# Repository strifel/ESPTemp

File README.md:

# ESPTemp

A small ambient sensor PCB powered by an ESP32-C3 an BME280 or BME680

## Parts

| **Part** |  **Description** |
| -------- | ---------------- |
| U1       | ESP32-C3-WROOM   |
| U2       | TLV1117-3.3V     |
| U3       | BME280           |
| U4       | BME680           |
| D1       | WS2812B LED      |
| R1,R2    | 5.1k Resistor    |
| R3,R5,R6 | 10k Resistor     |
| R4       | 1k Resistor      |
| C1,C4    | 100 uF Capacitor |
| C2       | 1 uF Capacitor   |
| C4       | 10 uF Capacitor  |
| J1       | USB_C_Receptable |
| J2       | 3-Pin-Connector  |

## Software

As [ESPHome](https://esphome.io/) does support the BME280/BME680 it is recommended to use ESPHome.

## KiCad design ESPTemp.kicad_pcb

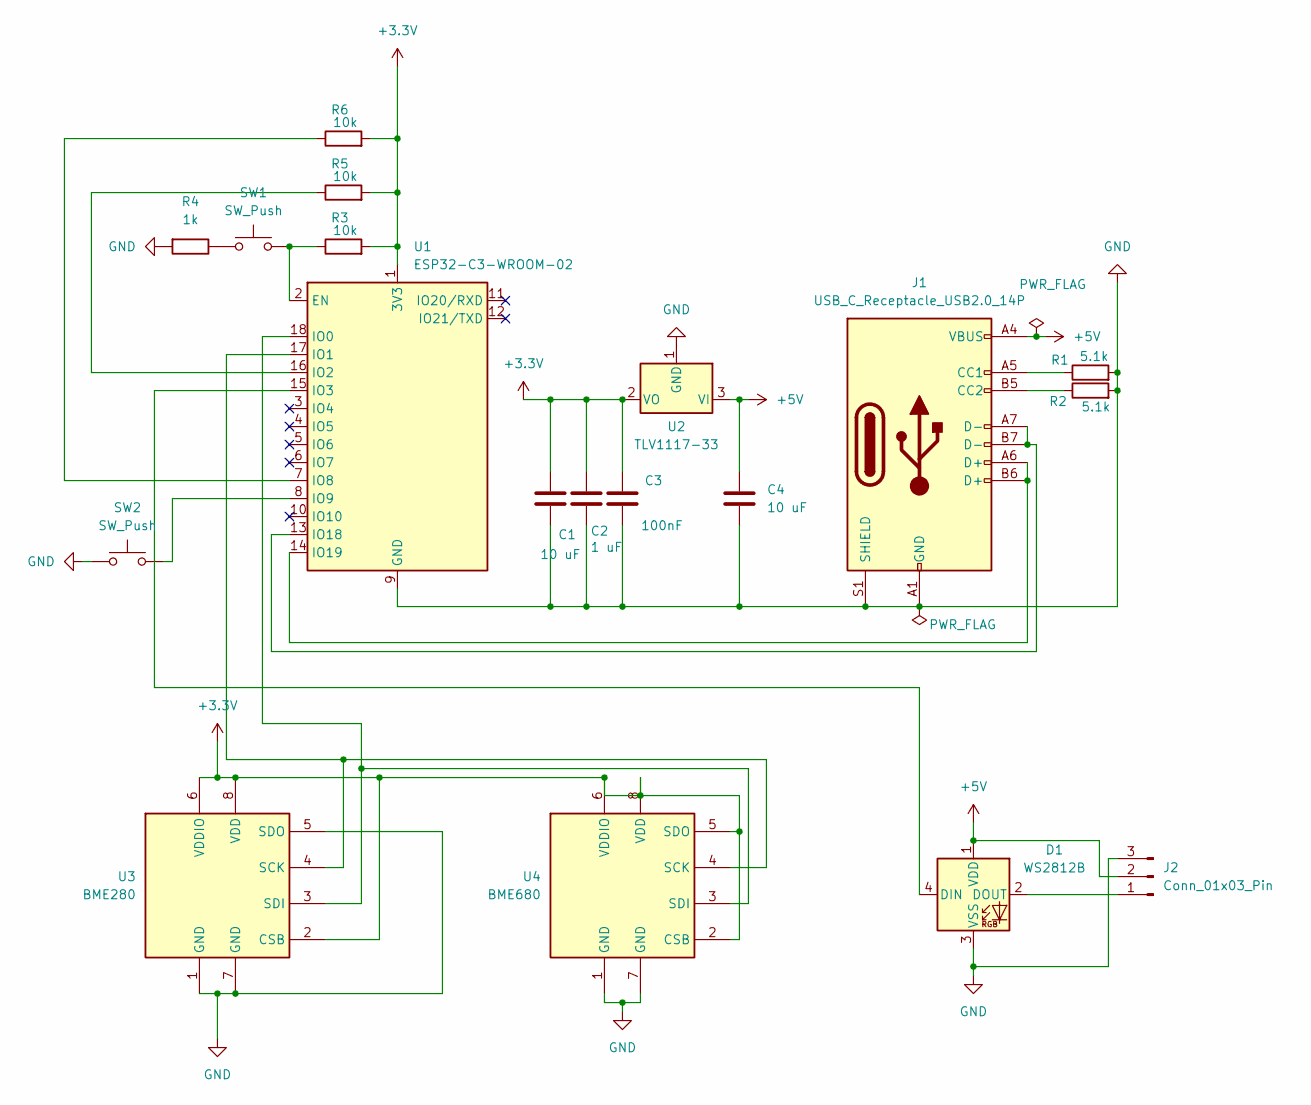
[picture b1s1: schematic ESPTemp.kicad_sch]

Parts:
C1, C4: 10 uF; C_0603_1608Metric_Pad1.08x0.95mm_HandSolder; LCSC C85713
C2: 1 uF; C_0603_1608Metric_Pad1.08x0.95mm_HandSolder; LCSC C6119865
C3: 100nF; C_0603_1608Metric_Pad1.08x0.95mm_HandSolder; LCSC C14663
D1: WS2812B; LED_WS2812B_PLCC4_5.0x5.0mm_P3.2mm; LCSC C2874885
J1: USB_C_Receptacle_USB2.0_14P; USB_C_Receptacle_HRO_TYPE-C-31-M-12; LCSC C2765186
J2: Conn_01x03_Pin; PinSocket_1x03_P2.54mm_Vertical_SMD_Pin1Left
R1, R2: 5.1k; R_0603_1608Metric_Pad0.98x0.95mm_HandSolder; LCSC C23186
R3, R5, R6: 10k; R_0603_1608Metric_Pad0.98x0.95mm_HandSolder; LCSC C25804
R4: 1k; R_0603_1608Metric_Pad0.98x0.95mm_HandSolder; LCSC C2907113
SW1, SW2: SW_Push; SW_Push_SPST_NO_Alps_SKRK; LCSC C2874432
U1: ESP32-C3-WROOM-02
U2: TLV1117-33; SOT-223-3_TabPin2; LCSC Part # C91728
U3: BME280; Bosch_LGA-8_2.5x2.5mm_P0.65mm_ClockwisePinNumbering; MPN C92489
U4: BME680; Bosch_LGA-8_3x3mm_P0.8mm_ClockwisePinNumbering

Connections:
+3.3V: C1.1, C2.1, C3.1, R3.2, R5.2, R6.2, U1.1 (3V3), U2.2 (VO), U3.2 (CSB), U3.6 (VDDIO), U3.8 (VDD), U4.2 (CSB), U4.5 (SDO), U4.6 (VDDIO), U4.8 (VDD)
+5V: C4.1, D1.1 (VDD), J1.A4 (VBUS), J1.A9 (VBUS), J1.B4 (VBUS), J1.B9 (VBUS), J2.2, U2.3 (VI)
GND: C1.2, C2.2, C3.2, C4.2, D1.3 (VSS), J1.A1 (GND), J1.A12 (GND), J1.B1 (GND), J1.B12 (GND), J1.S1 (SHIELD), J2.3, R1.2, R2.2, R4.2, SW2.1, U1.9 (GND), U1.19 (GND), U2.1 (GND), U3.1 (GND), U3.5 (SDO), U3.7 (GND), U4.1 (GND), U4.7 (GND)
unnamed: D1.4 (DIN), U1.15 (IO3)
unnamed: D1.2 (DOUT), J2.1
unnamed: J1.A5 (CC1), R1.1
unnamed: J1.B5 (CC2), R2.1
unnamed: R4.1, SW1.1
unnamed: R3.1, SW1.2, U1.2 (EN)
unnamed: U1.18 (IO0), U3.3 (SDI), U4.3 (SDI)
unnamed: U1.17 (IO1), U3.4 (SCK), U4.4 (SCK)
unnamed: R5.1, U1.16 (IO2)
unnamed: R6.1, U1.7 (IO8)
unnamed: SW2.2, U1.8 (IO9)
unnamed: J1.A7 (D-), J1.B7 (D-), U1.13 (IO18)
unnamed: J1.A6 (D+), J1.B6 (D+), U1.14 (IO19)

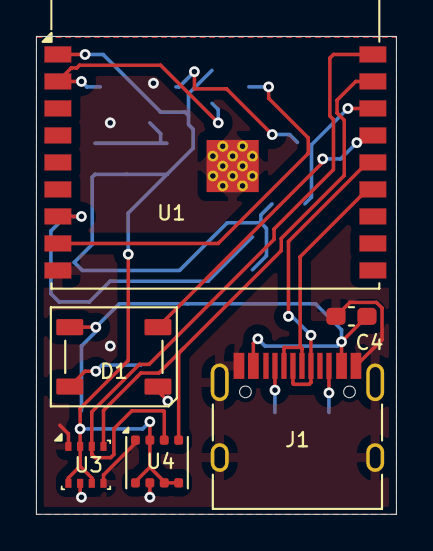
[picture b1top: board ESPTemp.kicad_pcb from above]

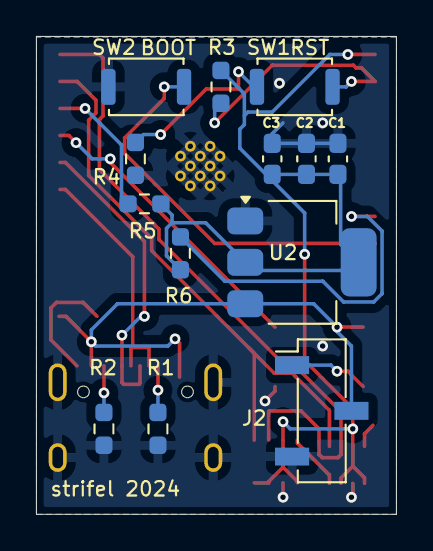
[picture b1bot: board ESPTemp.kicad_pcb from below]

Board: 2 copper layers, 20.0 x 26.5 mm, 19 parts (13 on the bottom side), 16 nets.
